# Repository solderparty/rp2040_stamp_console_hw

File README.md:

# RP2040 Stamp Handheld Console (Flux Project)

This Flux project transforms an RP2040 Stamp into a small handheld console with a **1.3" 128x64 OLED**, D-pad + A and B buttons, **RGB LED**, a **Qwiic** connector, a power switch, and a **speaker**.

As the console is powered by the Stamp, you can run **CircuitPython** on it, as well as **Arduino**, including experimental support for the **Arduboy2** library.

# Details

To make it truly portable, you will need a battery. This product does not ship with one, you can use any 3.7V/4.2V LiPo that is around or smaller than 40x30 mm. We recommend the [500mAh LiPo from Pimoroni](https://shop.pimoroni.com/products/lipo-battery-pack?variant=20429082055).

You can find a 3D-printable model for the case on [Printables](https://www.printables.com/model/279210-rp2040-stamp-handheld-console-case). You will also need four M2x4 screws and four M2 threaded inserts. 

# What does "Flux Project" mean?

At Solder Party, we always want to get interesting products in people's hands. However, releasing a product is no easy feat, we need to make sure everything is polished, provide documentation, examples, and extensive support.

With Flux, we want to streamline the process a bit, get fun projects into everyone's hands quicker.

Flux projects are more experimental in nature. While they are tested and verified, the documentation might not be fully there, and the examples might be very basic. 
Flux projects are targeted at people who are not scared to put a bit of extra work into getting the project to where they want it to end up.
These projects are also produced in smaller quantities, there is no guarantee there will be more produced in the future. Even if there is a new batch, it might differ from the initial version. 

These projects are in constant Flux, so to speak.

If there is enough interest, a Flux project might become a fully-fledged Solder Party product in the future, but there is no guarantee.

# Links

For more information visit https://flux.solder.party/

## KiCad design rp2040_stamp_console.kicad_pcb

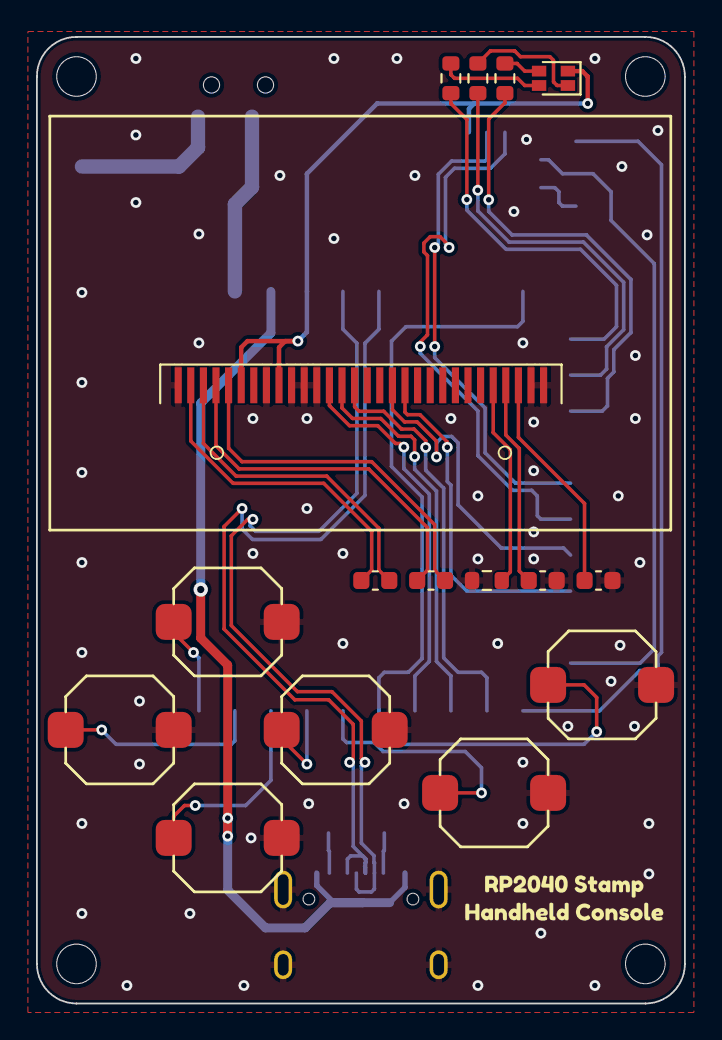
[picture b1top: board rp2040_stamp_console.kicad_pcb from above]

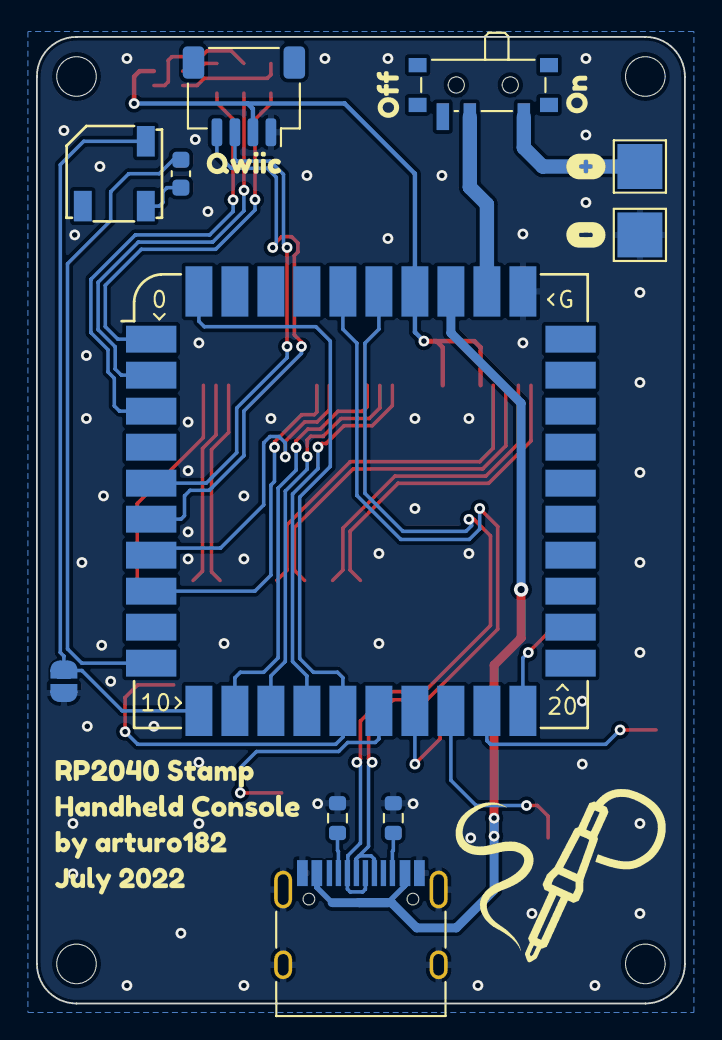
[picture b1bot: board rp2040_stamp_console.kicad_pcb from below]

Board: 2 copper layers, 36.0 x 53.7 mm, 35 parts (17 on the bottom side), 38 nets.

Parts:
C1: 4.7uF; C_0603_1608Metric
C2, C3, C4, C5: 1uF; C_0603_1608Metric
D1: LED_BAGR; LED_RGBA_0606
DS1: OLED-128O064D
J1: USB_C_Receptacle_USB2.0; USB_C_Receptacle_HRO_TYPE-C-31-M-12
J2: Conn_Qwiic; JST_SH_SM04B-SRSS-TB_1x04-1MP_P1.00mm_Horizontal
JP1: SJ_LOUDER; SolderJumper-2_P1.3mm_Open_RoundedPad1.0x1.5mm
LS1: Speaker; CMT-5023S
R1, R2, R3: 2K; R_0603_1608Metric
R4, R5: 5.1K; R_0603_1608Metric
R6: 390K; R_0603_1608Metric
SW1: SW_UP; RMT-CZ66
SW2: SW_DOWN; RMT-CZ66
SW3: SW_LEFT; RMT-CZ66
SW4: SW_RIGHT; RMT-CZ66
SW5: SW_A; RMT-CZ66
SW6: SW_B; RMT-CZ66
SW7: SW_POWER; SW_SPDT_PCM12
TP1: TP_BATT+; TestPoint_Pad_2.5x2.5mm
TP2: TP_BATT-; TestPoint_Pad_2.5x2.5mm
U1: RP2040_Stamp; RP2040_Stamp_SMD
kibuzzard-62C6F28A: G***; kibuzzard-62C6F28A
kibuzzard-62C56D6F, kibuzzard-62C56D6F#2: G***; kibuzzard-62C56D6F
kibuzzard-62C5723D: G***; kibuzzard-62C5723D
kibuzzard-62C57215: G***; kibuzzard-62C57215
kibuzzard-62DEDED4: G***; kibuzzard-62DEDED4
kibuzzard-62DEDF00: G***; kibuzzard-62DEDF00
kibuzzard-62DEDF0B: G***; kibuzzard-62DEDF0B

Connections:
+3.3V: D1.3 (A), DS1.6 (VBAT), DS1.9 (VDD), J2.2, U1.34 (3.3V)
+5V: J1.A4 (VBUS), J1.A9 (VBUS), J1.B4 (VBUS), J1.B9 (VBUS), U1.33 (5V)
+BATT: SW7.1 (A), TP1.1
/BATT: SW7.2 (B), U1.32 (VBAT)
/BOOTSEL: SW6.1 (A), U1.15 (GPIO14), U1.40 (BOOTSEL)
/BTN_A: SW5.1 (A), U1.16 (GPIO15)
/BTN_DOWN: SW2.1 (A), U1.18 (GPIO17)
/BTN_LEFT: SW3.1 (A), U1.19 (GPIO18)
/BTN_RIGHT: SW4.1 (A), U1.17 (GPIO16)
/BTN_UP: SW1.1 (A), U1.20 (GPIO19)
/LCD_CLK: DS1.18 (D0), U1.7 (GPIO6)
/LCD_CS: DS1.13 (~CS), U1.14 (GPIO13)
/LCD_DC: DS1.15 (D/~C), U1.12 (GPIO11)
/LCD_MOSI: DS1.19 (D1), U1.8 (GPIO7)
/LCD_RST: DS1.14 (~RES), U1.13 (GPIO12)
/LED_B: R1.1, U1.3 (GPIO2)
/LED_G: R3.1, U1.1 (GPIO0)
/LED_R: R2.1, U1.2 (GPIO1)
/SCL: J2.4, U1.6 (GPIO5)
/SDA: J2.3, U1.5 (GPIO4)
/SPK+: C1.1, U1.10 (GPIO9)
/SPK-: JP1.1 (A), LS1.2, U1.11 (GPIO10)
/USB_D+: J1.A6 (D+), J1.B6 (D+), U1.36 (USB_D+)
/USB_D-: J1.A7 (D-), J1.B7 (D-), U1.35 (USB_D-)
GND: C2.1, C5.2, DS1.1 (GND), DS1.8 (VSS), DS1.10 (BS0), DS1.11 (BS1), DS1.12 (BS2), DS1.29 (VLSS), DS1.30 (GND), J1.A1 (GND), J1.A12 (GND), J1.B1 (GND), J1.B12 (GND), J1.S1 (SHIELD), J2.1, JP1.2 (B), R4.2, R5.2, R6.2, SW1.2 (B), SW2.2 (B), SW3.2 (B), SW4.2 (B), SW5.2 (B), SW6.2 (B), TP2.1, U1.31 (GND)
unnamed: C1.2, LS1.1
unnamed: C2.2, DS1.28 (VCC)
unnamed: C3.1, DS1.2 (C2N)
unnamed: C3.2, DS1.3 (C2P)
unnamed: C4.1, DS1.4 (C1P)
unnamed: C4.2, DS1.5 (C1N)
unnamed: C5.1, DS1.27 (VCOMH)
unnamed: D1.1 (GK), R3.2
unnamed: D1.2 (BK), R1.2
unnamed: D1.4 (RK), R2.2
unnamed: DS1.26 (IREF), R6.1
unnamed: J1.A5 (CC1), R4.1
unnamed: J1.B5 (CC2), R5.1

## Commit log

2022-07-07 Rev 1
2022-09-21 Rev 2
